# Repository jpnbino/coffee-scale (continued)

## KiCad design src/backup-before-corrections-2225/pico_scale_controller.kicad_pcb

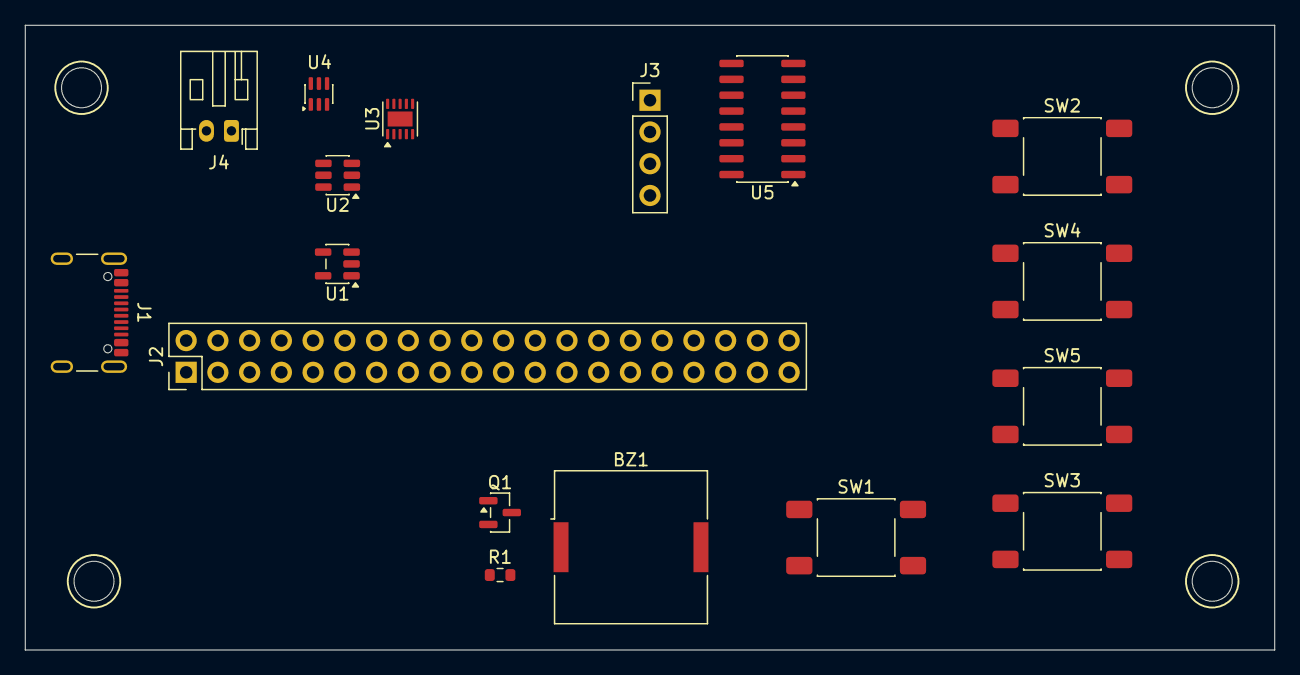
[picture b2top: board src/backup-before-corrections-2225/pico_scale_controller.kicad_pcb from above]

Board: 2 copper layers, 100.0 x 50.0 mm, 21 parts (0 on the bottom side), 3 nets, no tracks yet.

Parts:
BZ1: Buzzer; Buzzer_Murata_PKLCS1212E
H1, H2, H3, H4: MountingHole_3.2mm_M3
J1: USB_C_Receptacle_PowerOnly_6P; USB_C_Receptacle_GCT_USB4105-xx-A_16P_TopMnt_Horizontal
J2: Conn_02x20_Odd_Even; PinHeader_2x20_P2.54mm_Vertical
J3: Conn_01x04_Pin; PinHeader_1x04_P2.54mm_Vertical
J4: Conn_01x02; JST_PH_S2B-PH-K_1x02_P2.00mm_Horizontal
Q1: Q_NMOS_GSD; SOT-23
R1: R; R_0603_1608Metric
SW1, SW2, SW3, SW4, SW5: SW_Push; SW_Push_1P1T_NO_E-Switch_TL3301NxxxxxG
U1: MCP73831-2-OT; SOT-23-5
U2: DW01A; SOT-23-6
U3: TPS63031DSK; WSON-10-1EP_2.5x2.5mm_P0.5mm_EP1.2x2mm
U4: TPS22919DCK; SOT-363_SC-70-6
U5: HX711; SOIC-16_3.9x9.9mm_P1.27mm

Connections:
unnamed: J1.A12 (GND), J1.B12 (GND)
unnamed: J1.A9 (VBUS), J1.B9 (VBUS)
unnamed: U3.3 (PGND), U3.11 (PGND)
